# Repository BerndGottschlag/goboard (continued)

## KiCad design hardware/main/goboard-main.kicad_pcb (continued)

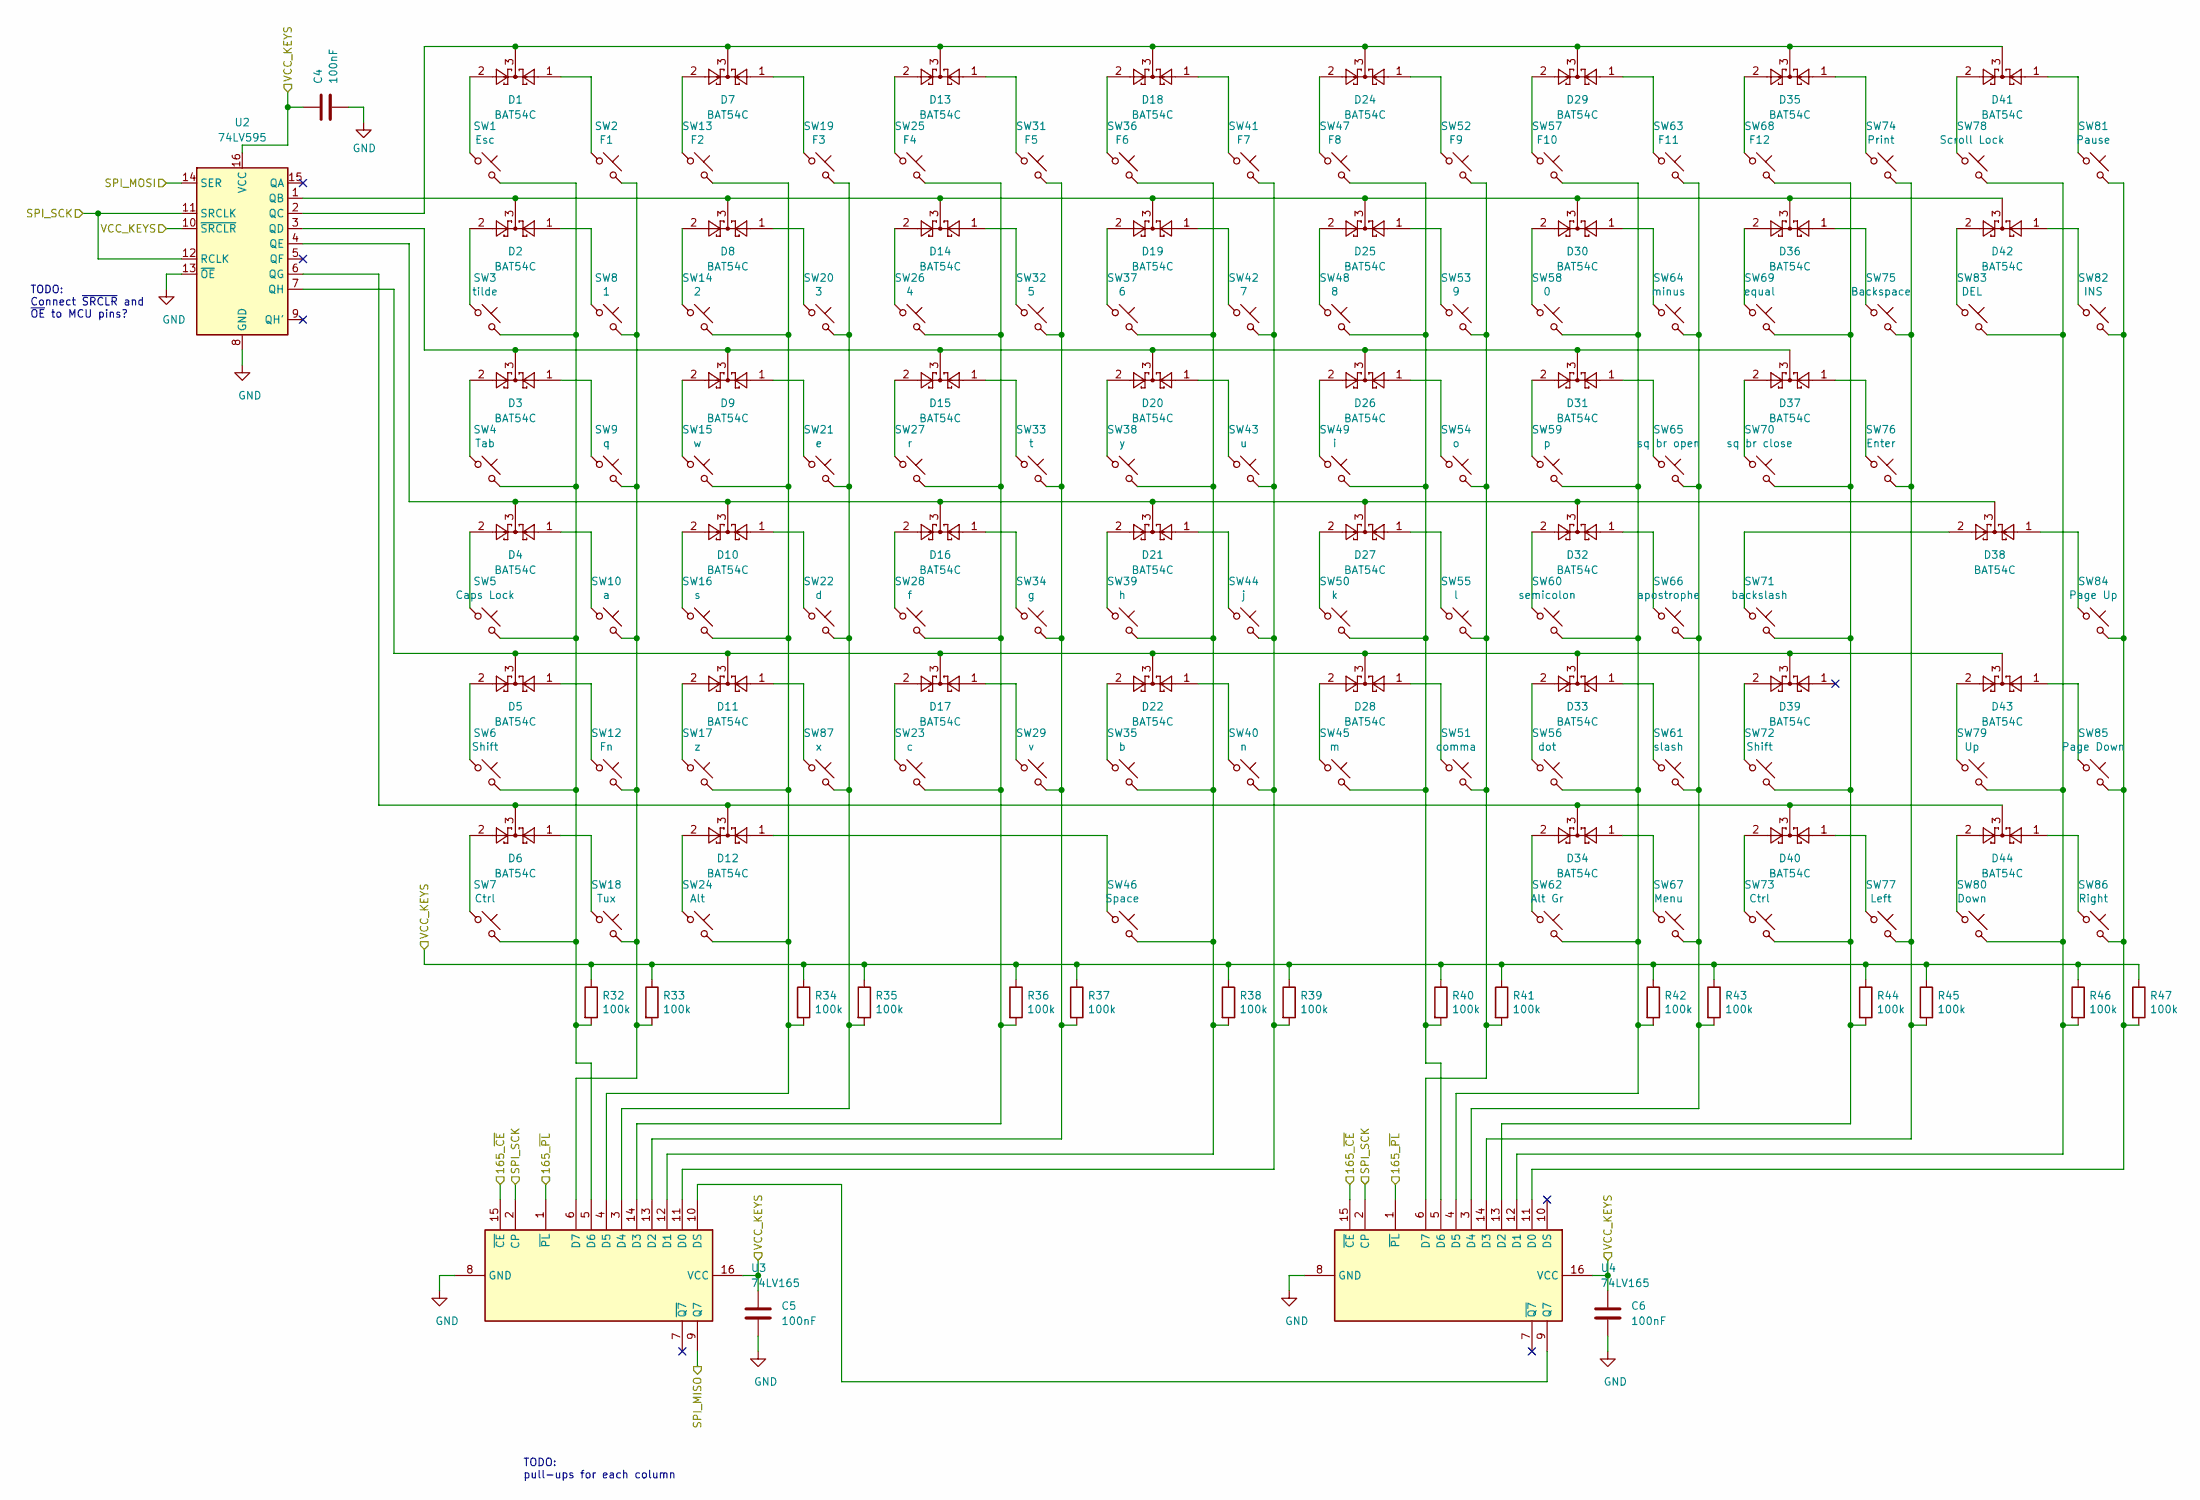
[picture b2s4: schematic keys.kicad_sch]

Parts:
C4, C5, C6: 100nF; C_0603_1608Metric_Pad1.08x0.95mm_HandSolder; Part Name 06033C104KAT4A; Mouser 581-06033C104KAT4A
D1, D2, D3, D4, D5, D6, D7, D8, D9, D10, D11, D12, D13, D14, D15, D16, D17, D18, D19, D20, D21, D22, D24, D25, D26, D27, D28, D29, D30, D31, D32, D33, D34, D35, D36, D37, D38, D39, D40, D41, D42, D43, D44: BAT54C; SOT-23; Part Name BAT54A; Mouser 241-BAT54A_R1_00001
R32, R33, R34, R35, R36, R37, R38, R39, R40, R41, R42, R43, R44, R45, R46, R47: 100k; R_0603_1608Metric_Pad0.98x0.95mm_HandSolder
SW1: Esc; SW_Cherry_MX_1.00u_PCB; Part Name MX1A-E1NW; Mouser 540-MX1A-E1NW
SW2: F1; SW_Cherry_MX_1.00u_PCB; Part Name MX1A-E1NW; Mouser 540-MX1A-E1NW
SW3: tilde; SW_Cherry_MX_1.00u_PCB; Part Name MX1A-E1NW; Mouser 540-MX1A-E1NW
SW4: Tab; SW_Cherry_MX_1.50u_PCB; Part Name MX1A-E1NW; Mouser 540-MX1A-E1NW
SW5: Caps Lock; SW_Cherry_MX_1.75u_PCB; Part Name MX1A-E1NW; Mouser 540-MX1A-E1NW
SW6: Shift; SW_Cherry_MX_1.25u_PCB; Part Name MX1A-E1NW; Mouser 540-MX1A-E1NW
SW7: Ctrl; SW_Cherry_MX_1.25u_PCB; Part Name MX1A-E1NW; Mouser 540-MX1A-E1NW
SW8: 1; SW_Cherry_MX_1.00u_PCB; Part Name MX1A-E1NW; Mouser 540-MX1A-E1NW
SW9: q; SW_Cherry_MX_1.00u_PCB; Part Name MX1A-E1NW; Mouser 540-MX1A-E1NW
SW10: a; SW_Cherry_MX_1.00u_PCB; Part Name MX1A-E1NW; Mouser 540-MX1A-E1NW
SW12: Fn; SW_Cherry_MX_1.00u_PCB; Part Name MX1A-E1NW; Mouser 540-MX1A-E1NW
SW13: F2; SW_Cherry_MX_1.00u_PCB; Part Name MX1A-E1NW; Mouser 540-MX1A-E1NW
SW14: 2; SW_Cherry_MX_1.00u_PCB; Part Name MX1A-E1NW; Mouser 540-MX1A-E1NW
SW15: w; SW_Cherry_MX_1.00u_PCB; Part Name MX1A-E1NW; Mouser 540-MX1A-E1NW
SW16: s; SW_Cherry_MX_1.00u_PCB; Part Name MX1A-E1NW; Mouser 540-MX1A-E1NW
SW17: z; SW_Cherry_MX_1.00u_PCB; Part Name MX1A-E1NW; Mouser 540-MX1A-E1NW
SW18: Tux; SW_Cherry_MX_1.25u_PCB; Part Name MX1A-E1NW; Mouser 540-MX1A-E1NW
SW19: F3; SW_Cherry_MX_1.00u_PCB; Part Name MX1A-E1NW; Mouser 540-MX1A-E1NW
SW20: 3; SW_Cherry_MX_1.00u_PCB; Part Name MX1A-E1NW; Mouser 540-MX1A-E1NW
SW21: e; SW_Cherry_MX_1.00u_PCB; Part Name MX1A-E1NW; Mouser 540-MX1A-E1NW
SW22: d; SW_Cherry_MX_1.00u_PCB; Part Name MX1A-E1NW; Mouser 540-MX1A-E1NW
SW23: c; SW_Cherry_MX_1.00u_PCB; Part Name MX1A-E1NW; Mouser 540-MX1A-E1NW
SW24: Alt; SW_Cherry_MX_1.25u_PCB; Part Name MX1A-E1NW; Mouser 540-MX1A-E1NW
SW25: F4; SW_Cherry_MX_1.00u_PCB; Part Name MX1A-E1NW; Mouser 540-MX1A-E1NW
SW26: 4; SW_Cherry_MX_1.00u_PCB; Part Name MX1A-E1NW; Mouser 540-MX1A-E1NW
SW27: r; SW_Cherry_MX_1.00u_PCB; Part Name MX1A-E1NW; Mouser 540-MX1A-E1NW
SW28: f; SW_Cherry_MX_1.00u_PCB; Part Name MX1A-E1NW; Mouser 540-MX1A-E1NW
SW29: v; SW_Cherry_MX_1.00u_PCB; Part Name MX1A-E1NW; Mouser 540-MX1A-E1NW
SW31: F5; SW_Cherry_MX_1.00u_PCB; Part Name MX1A-E1NW; Mouser 540-MX1A-E1NW
SW32: 5; SW_Cherry_MX_1.00u_PCB; Part Name MX1A-E1NW; Mouser 540-MX1A-E1NW
SW33: t; SW_Cherry_MX_1.00u_PCB; Part Name MX1A-E1NW; Mouser 540-MX1A-E1NW
SW34: g; SW_Cherry_MX_1.00u_PCB; Part Name MX1A-E1NW; Mouser 540-MX1A-E1NW
SW35: b; SW_Cherry_MX_1.00u_PCB; Part Name MX1A-E1NW; Mouser 540-MX1A-E1NW
SW36: F6; SW_Cherry_MX_1.00u_PCB; Part Name MX1A-E1NW; Mouser 540-MX1A-E1NW
SW37: 6; SW_Cherry_MX_1.00u_PCB; Part Name MX1A-E1NW; Mouser 540-MX1A-E1NW
SW38: y; SW_Cherry_MX_1.00u_PCB; Part Name MX1A-E1NW; Mouser 540-MX1A-E1NW
SW39: h; SW_Cherry_MX_1.00u_PCB; Part Name MX1A-E1NW; Mouser 540-MX1A-E1NW
SW40: n; SW_Cherry_MX_1.00u_PCB; Part Name MX1A-E1NW; Mouser 540-MX1A-E1NW
SW41: F7; SW_Cherry_MX_1.00u_PCB; Part Name MX1A-E1NW; Mouser 540-MX1A-E1NW
SW42: 7; SW_Cherry_MX_1.00u_PCB; Part Name MX1A-E1NW; Mouser 540-MX1A-E1NW
SW43: u; SW_Cherry_MX_1.00u_PCB; Part Name MX1A-E1NW; Mouser 540-MX1A-E1NW
SW44: j; SW_Cherry_MX_1.00u_PCB; Part Name MX1A-E1NW; Mouser 540-MX1A-E1NW
SW45: m; SW_Cherry_MX_1.00u_PCB; Part Name MX1A-E1NW; Mouser 540-MX1A-E1NW
SW46: Space; SW_Cherry_MX_6.25u_PCB; Part Name MX1A-E1NW; Mouser 540-MX1A-E1NW
SW47: F8; SW_Cherry_MX_1.00u_PCB; Part Name MX1A-E1NW; Mouser 540-MX1A-E1NW
SW48: 8; SW_Cherry_MX_1.00u_PCB; Part Name MX1A-E1NW; Mouser 540-MX1A-E1NW
SW49: i; SW_Cherry_MX_1.00u_PCB; Part Name MX1A-E1NW; Mouser 540-MX1A-E1NW
SW50: k; SW_Cherry_MX_1.00u_PCB; Part Name MX1A-E1NW; Mouser 540-MX1A-E1NW
SW51: comma; SW_Cherry_MX_1.00u_PCB; Part Name MX1A-E1NW; Mouser 540-MX1A-E1NW
SW52: F9; SW_Cherry_MX_1.00u_PCB; Part Name MX1A-E1NW; Mouser 540-MX1A-E1NW
SW53: 9; SW_Cherry_MX_1.00u_PCB; Part Name MX1A-E1NW; Mouser 540-MX1A-E1NW
SW54: o; SW_Cherry_MX_1.00u_PCB; Part Name MX1A-E1NW; Mouser 540-MX1A-E1NW
SW55: l; SW_Cherry_MX_1.00u_PCB; Part Name MX1A-E1NW; Mouser 540-MX1A-E1NW
SW56: dot; SW_Cherry_MX_1.00u_PCB; Part Name MX1A-E1NW; Mouser 540-MX1A-E1NW
SW57: F10; SW_Cherry_MX_1.00u_PCB; Part Name MX1A-E1NW; Mouser 540-MX1A-E1NW
SW58: 0; SW_Cherry_MX_1.00u_PCB; Part Name MX1A-E1NW; Mouser 540-MX1A-E1NW
SW59: p; SW_Cherry_MX_1.00u_PCB; Part Name MX1A-E1NW; Mouser 540-MX1A-E1NW
SW60: semicolon; SW_Cherry_MX_1.00u_PCB; Part Name MX1A-E1NW; Mouser 540-MX1A-E1NW
SW61: slash; SW_Cherry_MX_1.00u_PCB; Part Name MX1A-E1NW; Mouser 540-MX1A-E1NW
SW62: Alt Gr; SW_Cherry_MX_1.00u_PCB; Part Name MX1A-E1NW; Mouser 540-MX1A-E1NW
SW63: F11; SW_Cherry_MX_1.00u_PCB; Part Name MX1A-E1NW; Mouser 540-MX1A-E1NW
SW64: minus; SW_Cherry_MX_1.00u_PCB; Part Name MX1A-E1NW; Mouser 540-MX1A-E1NW
SW65: sq br open; SW_Cherry_MX_1.00u_PCB; Part Name MX1A-E1NW; Mouser 540-MX1A-E1NW
SW66: apostrophe; SW_Cherry_MX_1.00u_PCB; Part Name MX1A-E1NW; Mouser 540-MX1A-E1NW
SW67: Menu; SW_Cherry_MX_1.00u_PCB; Part Name MX1A-E1NW; Mouser 540-MX1A-E1NW
SW68: F12; SW_Cherry_MX_1.00u_PCB; Part Name MX1A-E1NW; Mouser 540-MX1A-E1NW
SW69: equal; SW_Cherry_MX_1.00u_PCB; Part Name MX1A-E1NW; Mouser 540-MX1A-E1NW
SW70: sq br close; SW_Cherry_MX_1.00u_PCB; Part Name MX1A-E1NW; Mouser 540-MX1A-E1NW
SW71: backslash; SW_Cherry_MX_1.00u_PCB; Part Name MX1A-E1NW; Mouser 540-MX1A-E1NW
SW72: Shift; SW_Cherry_MX_1.75u_PCB; Part Name MX1A-E1NW; Mouser 540-MX1A-E1NW
SW73: Ctrl; SW_Cherry_MX_1.00u_PCB; Part Name MX1A-E1NW; Mouser 540-MX1A-E1NW
SW74: Print; SW_Cherry_MX_1.00u_PCB; Part Name MX1A-E1NW; Mouser 540-MX1A-E1NW
SW75: Backspace; SW_Cherry_MX_2.00u_PCB; Part Name MX1A-E1NW; Mouser 540-MX1A-E1NW
SW76: Enter; SW_Cherry_MX_ISOEnter_PCB; Part Name MX1A-E1NW; Mouser 540-MX1A-E1NW
SW77: Left; SW_Cherry_MX_1.00u_PCB; Part Name MX1A-E1NW; Mouser 540-MX1A-E1NW
SW78: Scroll Lock; SW_Cherry_MX_1.00u_PCB; Part Name MX1A-E1NW; Mouser 540-MX1A-E1NW
SW79: Up; SW_Cherry_MX_1.00u_PCB; Part Name MX1A-E1NW; Mouser 540-MX1A-E1NW
SW80: Down; SW_Cherry_MX_1.00u_PCB; Part Name MX1A-E1NW; Mouser 540-MX1A-E1NW
SW81: Pause; SW_Cherry_MX_1.00u_PCB; Part Name MX1A-E1NW; Mouser 540-MX1A-E1NW
SW82: INS; SW_Cherry_MX_1.00u_PCB; Part Name MX1A-E1NW; Mouser 540-MX1A-E1NW
SW83: DEL; SW_Cherry_MX_1.00u_PCB; Part Name MX1A-E1NW; Mouser 540-MX1A-E1NW
SW84: Page Up; SW_Cherry_MX_1.00u_PCB; Part Name MX1A-E1NW; Mouser 540-MX1A-E1NW
SW85: Page Down; SW_Cherry_MX_1.00u_PCB; Part Name MX1A-E1NW; Mouser 540-MX1A-E1NW
SW86: Right; SW_Cherry_MX_1.00u_PCB; Part Name MX1A-E1NW; Mouser 540-MX1A-E1NW
SW87: x; SW_Cherry_MX_1.00u_PCB; Part Name MX1A-E1NW; Mouser 540-MX1A-E1NW
U2: 74LV595; TSSOP-16_4.4x5mm_P0.65mm; Mouser 771-74LV595PW-T
U3, U4: 74LV165; TSSOP-16_4.4x5mm_P0.65mm; Mouser 771-LV165PW112

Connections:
/MCU/165_~CE: U3.15 (~CE), U4.15 (~CE); also elsewhere on the board
/MCU/165_~PL: U3.1 (~PL), U4.1 (~PL); also elsewhere on the board
/MCU/SPI_MISO: U3.9 (Q7); also elsewhere on the board
/MCU/SPI_MOSI: U2.14 (SER); also elsewhere on the board
/MCU/SPI_SCK: U2.11 (SRCLK), U2.12 (RCLK), U3.2 (CP), U4.2 (CP); also elsewhere on the board
/VCC_KEYS: C4.1, C5.1, C6.1, R32.1, R33.1, R34.1, R35.1, R36.1, R37.1, R38.1, R39.1, R40.1, R41.1, R42.1, R43.1, R44.1, R45.1, R46.1, R47.1, U2.10 (~SRCLR), U2.16 (VCC), U3.16 (VCC), U4.16 (VCC); also elsewhere on the board
GND: C4.2, C5.2, C6.2, U2.8 (GND), U2.13 (~OE), U3.8 (GND), U4.8 (GND); also elsewhere on the board
unnamed: D1.1, SW2.1
unnamed: D1.2, SW1.1
unnamed: D1.3, D7.3, D13.3, D18.3, D24.3, D29.3, D35.3, D41.3, U2.2 (QC)
unnamed: D2.1, SW8.1
unnamed: D2.2, SW3.1
unnamed: D3.1, SW9.1
unnamed: D3.2, SW4.1
unnamed: D4.1, SW10.1
unnamed: D4.2, SW5.1
unnamed: D5.1, SW12.1
unnamed: D5.2, SW6.1
unnamed: D6.1, SW18.1
unnamed: D6.2, SW7.1
unnamed: D7.1, SW19.1
unnamed: D7.2, SW13.1
unnamed: D8.1, SW20.1
unnamed: D8.2, SW14.1
unnamed: D9.1, SW21.1
unnamed: D9.2, SW15.1
unnamed: D10.1, SW22.1
unnamed: D10.2, SW16.1
unnamed: D4.3, D10.3, D16.3, D21.3, D27.3, D32.3, D38.3, U2.4 (QE)
unnamed: D11.1, SW87.1
unnamed: D11.2, SW17.1
unnamed: D5.3, D11.3, D17.3, D22.3, D28.3, D33.3, D39.3, D43.3, U2.7 (QH)
unnamed: D12.1, SW46.1
unnamed: D12.2, SW24.1
unnamed: D6.3, D12.3, D34.3, D40.3, D44.3, U2.6 (QG)
unnamed: D13.1, SW31.1
unnamed: D13.2, SW25.1
unnamed: D14.1, SW32.1
unnamed: D14.2, SW26.1
unnamed: D2.3, D8.3, D14.3, D19.3, D25.3, D30.3, D36.3, D42.3, U2.1 (QB)
unnamed: D15.1, SW33.1
unnamed: D15.2, SW27.1
unnamed: D3.3, D9.3, D15.3, D20.3, D26.3, D31.3, D37.3, U2.3 (QD)
unnamed: D16.1, SW34.1
unnamed: D16.2, SW28.1
unnamed: D17.1, SW29.1
unnamed: D17.2, SW23.1
unnamed: D18.1, SW41.1
unnamed: D18.2, SW36.1
unnamed: D19.1, SW42.1
unnamed: D19.2, SW37.1
unnamed: D20.1, SW43.1
unnamed: D20.2, SW38.1
unnamed: D21.1, SW44.1
unnamed: D21.2, SW39.1
unnamed: D22.1, SW40.1
unnamed: D22.2, SW35.1
unnamed: D24.1, SW52.1
unnamed: D24.2, SW47.1
unnamed: D25.1, SW53.1
unnamed: D25.2, SW48.1
unnamed: D26.1, SW54.1
unnamed: D26.2, SW49.1
unnamed: D27.1, SW55.1
unnamed: D27.2, SW50.1
unnamed: D28.1, SW51.1
unnamed: D28.2, SW45.1
unnamed: D29.1, SW63.1
unnamed: D29.2, SW57.1
unnamed: D30.1, SW64.1
unnamed: D30.2, SW58.1
unnamed: D31.1, SW65.1
unnamed: D31.2, SW59.1
unnamed: D32.1, SW66.1
unnamed: D32.2, SW60.1
unnamed: D33.1, SW61.1
unnamed: D33.2, SW56.1
unnamed: D34.1, SW67.1
unnamed: D34.2, SW62.1
unnamed: D35.1, SW74.1
unnamed: D35.2, SW68.1
unnamed: D36.1, SW75.1
unnamed: D36.2, SW69.1
unnamed: D37.1, SW76.1
unnamed: D37.2, SW70.1
unnamed: D38.1, SW84.1
unnamed: D38.2, SW71.1
unnamed: D39.2, SW72.1
unnamed: D40.1, SW77.1
unnamed: D40.2, SW73.1
unnamed: D41.1, SW81.1
unnamed: D41.2, SW78.1
unnamed: D42.1, SW82.1
unnamed: D42.2, SW83.1
unnamed: D43.1, SW85.1
unnamed: D43.2, SW79.1
unnamed: D44.1, SW86.1
unnamed: D44.2, SW80.1
unnamed: R32.2, SW1.2, SW3.2, SW4.2, SW5.2, SW6.2, SW7.2, U3.5 (D6)
unnamed: R33.2, SW2.2, SW8.2, SW9.2, SW10.2, SW12.2, SW18.2, U3.6 (D7)
unnamed: R34.2, SW13.2, SW14.2, SW15.2, SW16.2, SW17.2, SW24.2, U3.4 (D5)
unnamed: R35.2, SW19.2, SW20.2, SW21.2, SW22.2, SW87.2, U3.3 (D4)
unnamed: R36.2, SW23.2, SW25.2, SW26.2, SW27.2, SW28.2, U3.14 (D3)
unnamed: R37.2, SW29.2, SW31.2, SW32.2, SW33.2, SW34.2, U3.13 (D2)
unnamed: R38.2, SW35.2, SW36.2, SW37.2, SW38.2, SW39.2, SW46.2, U3.12 (D1)
unnamed: R39.2, SW40.2, SW41.2, SW42.2, SW43.2, SW44.2, U3.11 (D0)
unnamed: R40.2, SW45.2, SW47.2, SW48.2, SW49.2, SW50.2, U4.5 (D6)
unnamed: R41.2, SW51.2, SW52.2, SW53.2, SW54.2, SW55.2, U4.6 (D7)
unnamed: R42.2, SW56.2, SW57.2, SW58.2, SW59.2, SW60.2, SW62.2, U4.4 (D5)
unnamed: R43.2, SW61.2, SW63.2, SW64.2, SW65.2, SW66.2, SW67.2, U4.3 (D4)
unnamed: R44.2, SW68.2, SW69.2, SW70.2, SW71.2, SW72.2, SW73.2, U4.13 (D2)
unnamed: R45.2, SW74.2, SW75.2, SW76.2, SW77.2, U4.14 (D3)
unnamed: R46.2, SW78.2, SW79.2, SW80.2, SW83.2, U4.12 (D1)
unnamed: R47.2, SW81.2, SW82.2, SW84.2, SW85.2, SW86.2, U4.11 (D0)
unnamed: U3.10 (DS), U4.9 (Q7)

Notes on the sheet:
TODO: Connect ~SRCLR and ~OE to MCU pins?
TODO: pull-ups for each column

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
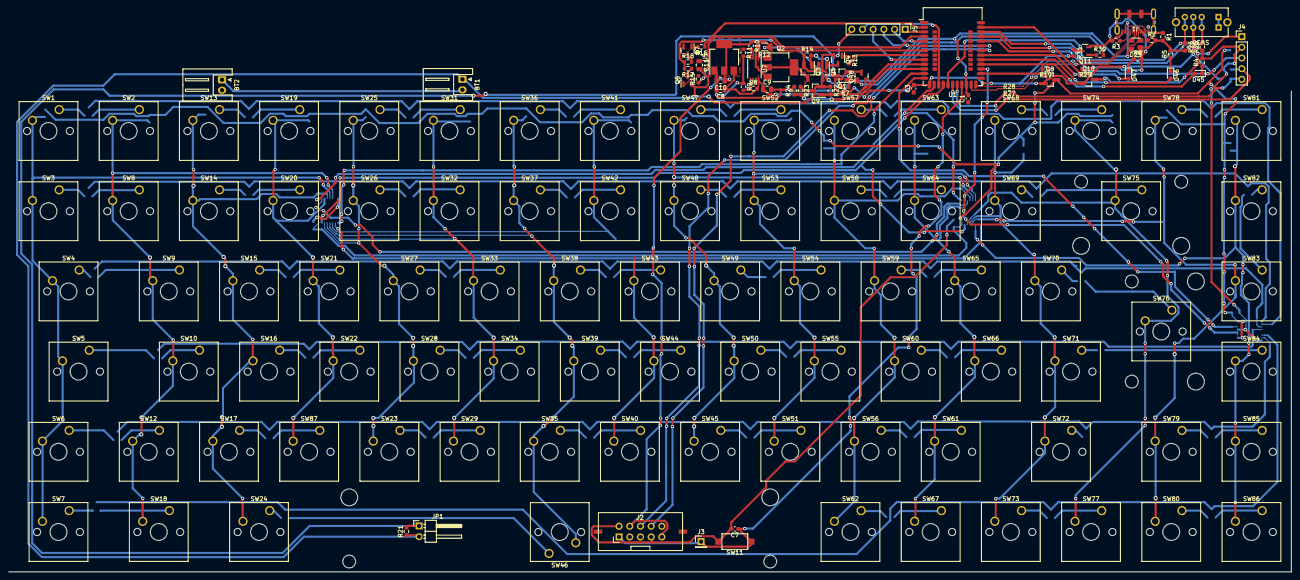
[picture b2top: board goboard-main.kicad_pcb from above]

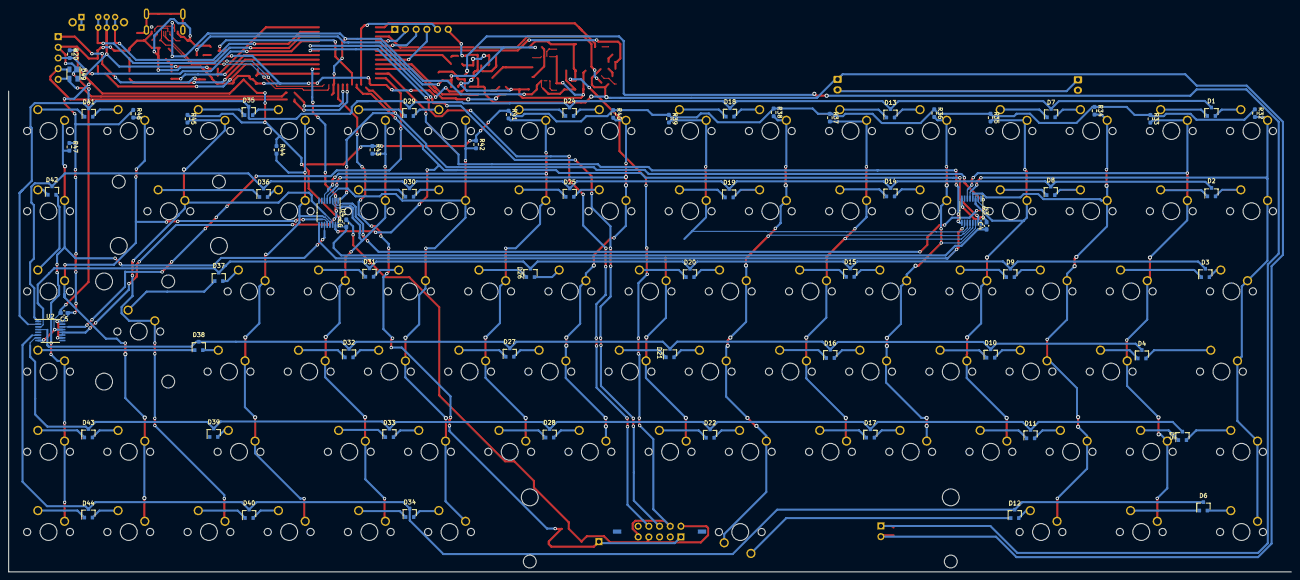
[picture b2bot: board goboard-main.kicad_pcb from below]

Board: 2 copper layers, 218 parts (67 on the bottom side), 171 nets.

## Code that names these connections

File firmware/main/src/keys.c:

#include "keys.h"

#include "app_timer.h"
#include "nrf_gpio.h"
#include "nrf_drv_spi.h"

#include <string.h>

#ifdef TEST_SETUP

#define TEST_KEY NRF_GPIO_PIN_MAP(1, 2)

#else

#define SPI_SCK_PIN NRF_GPIO_PIN_MAP(1, 0)
#define SPI_MISO_PIN NRF_GPIO_PIN_MAP(0, 4)
#define SPI_MOSI_PIN NRF_GPIO_PIN_MAP(0, 5)
#define LOAD_PIN NRF_GPIO_PIN_MAP(0, 7)
#define STORE_PIN NRF_GPIO_PIN_MAP(0, 12)

#define NUMPAD_RX_PIN NRF_GPIO_PIN_MAP(0, 21)
#define NUMPAD_TX_PIN NRF_GPIO_PIN_MAP(0, 19)
#define NUMPAD_ID_PIN NRF_GPIO_PIN_MAP(1, 4)

#define ENABLE_KEY_POWER_PIN NRF_GPIO_PIN_MAP(0, 22)
#define ENABLE_NUMPAD_POWER_PIN NRF_GPIO_PIN_MAP(1, 4)

/**
 * SPI for the key matrix shift registers.
 */
static const nrf_drv_spi_t spi = NRF_DRV_SPI_INSTANCE(0);

#endif

/**
 * Timer for periodic sampling of the numpad ID line.
 */
APP_TIMER_DEF(numpad_id_timer);

static struct key_bitmap key_state = EMPTY_KEY_BITMAP;

void key_bitmap_set(struct key_bitmap *bitmap, int scancode) {
	uint32_t word = scancode >> 5;
	uint32_t bit = scancode & 0x1f;
	bitmap->keys[word] |= 1 << bit;
}

void key_bitmap_clear(struct key_bitmap *bitmap, int scancode) {
	uint32_t word = scancode >> 5;
	uint32_t bit = scancode & 0x1f;
	bitmap->keys[word] &= ~(1 << bit);
}

void legacy_key_list_from_bitmap(const struct key_bitmap *bitmap,
                                 struct legacy_key_list *list) {
	/* TODO */
}

static void numpad_id_timer_handler(void *context) {
	/* TODO */
}

void keys_init(void) {
	ret_code_t ret;

	ret = app_timer_create(&numpad_id_timer,
	                       APP_TIMER_MODE_REPEATED,
	                       numpad_id_timer_handler);
	APP_ERROR_CHECK(ret);

	/* TODO */
}

void keys_activate(void) {
	/* TODO */
}

void keys_deactivate(void) {
	/* TODO */
}

void keys_activate_numpad(void) {
	/* TODO */
}

void keys_deactivate_numpad(void) {
	/* TODO */
}

void keys_set_num_lock_led(bool state) {
	/* TODO */
}

void keys_get_state(struct key_bitmap *bitmap) {
	memcpy(bitmap, &key_state, sizeof(key_state));
}

bool keys_poll(bool pause) {
	struct key_bitmap previous_key_state = key_state;

#ifdef TEST_SETUP
	bool test_key_state = nrf_gpio_pin_read(TEST_KEY);
	if (test_key_state) {
		key_bitmap_set(&key_state, KEY_K);
	} else {
		key_bitmap_clear(&key_state, KEY_K);
	}
	/* TODO: debouncing, pause */
#else
	/* TODO */
#endif
	return memcmp(&key_state, &previous_key_state, sizeof(key_state)) != 0;
}

void keys_prepare_system_off(void) {
	/* TODO */
}

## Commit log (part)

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2020-12-23 hardware: Add empty Kicad projects.
2020-12-23 Add README/LICENSE.
2020-12-25 Add keyboard layout and necessary 3d packages
2020-12-28 Implement the key matrix on the PCB
2020-12-29 Add a symbol for the Holyiot-18010-NRF52840
2020-12-29 Add footprint for the Holyiot-18010-NRF5284
2020-12-30 Add first schematic for the numpad
2020-12-31 Fix pin of the symbol of the Holyiot breakout board
2020-12-31 Add footprint for the USB-C jack JAE DX07S016JA1R1500
2021-01-01 Add 3d package for the usb jack
2021-01-01 Update the PCB
2021-01-01 Add connector to the numpad to the schematic
2021-01-01 WIP: numpad with an ATtiny
    As the newer versions of the ATtiny cannot be programmed using an
    In-Circuit-Programmer based on SPI this variant is not pursued further.
2021-01-02 Exchange the ATtiny with a STM32L011F4P6 for the numpad
2021-01-02 Modify the connection to the numpad
    As the numpad now uses a stm-microcontroller instead of the
    shift-registers the connection is changed to UART.
2021-01-02 Add programming/debug connection
2021-01-02 Fix MISO label for the shift registers
2021-01-02 Remove UART line from the NRF to the numpad
2021-01-02 Add footprints to many symbols
2021-01-02 Update PCB
2021-01-03 Add annotations
2021-01-03 Add specialized connector for the programming port
2021-01-09 Adapt the layout for another keycap set
    The layout is now compatible with this keycap set:
    https://hk-gaming.com/collections/keycaps/products/hk-gaming-dye-
    sublimation-cherry-profile-thick-pbt-keysets-for-mechanical-keyboard-139
    -keys-chalk
2021-01-09 Add outline of a shrouded pin header to the programming connector
2021-01-16 Add power supply from the debugging connector
    The batteries have to be disconnected when the debugger is plugged in,
    as the voltages differ (ca. 2V for the batteries, 3.3V for the
    debugger).
2021-01-16 Add kicad autosave files to gitignore
2021-01-16 Add new board outline
    Reason: This makes the first design iteration of the case possible.
2021-01-16 Add first rough version of the numpad PCB
2021-01-16 Redo board edge outline
2021-01-16 Fix path to the 3d model of the USB-C jack
2021-01-20 Write out the symbol names for the keys
2021-01-20 Add MCU-controlled battery balancing.
2021-01-20 Revert to a key layout with a menu key between alt gr and ctrl
2021-01-20 Fix power supply footprints and set references.
2021-01-23 Add signal to tell the MCU that USB is connected.
2021-01-24 Add footprint and 3D-model for the sliding switch
2021-01-24 Assign footprints
2021-01-24 Fix errors found by ERC
2021-01-25 Add an empty firmware project.
2021-01-25 Add circuit to disconnect the shift registers
    This is done to save energy when the keyboard is switched off.
2021-01-25 Add battery voltage measurement circuit
2021-01-25 Rework the off/bluetooth1/bluetooth2 switch connection
    To save energy an external pull-down resistor is added and the off
    position is not connected to the MCU.
2021-01-25 Remove the USB sense curcuit
    As V_BUS is connected to the MCU it can detect when the USB is
    connected.
2021-01-25 Rework the connection to the numpad
    Changes:
    - The UART lines now have a protection circuit
    - The power supply line of the numpad can be switched on and off by the MCU.
    - An Id-line is added so that the MCU can detect when the numpad is
    connected.
2021-01-25 Update the connection of the numpad
    The ID line is added to the numpad side and the connector pin assignment
    is updated.
2021-01-25 Fix symbol for the Holyiot board
    V_BUS pin was missing from the symbol.
2021-01-28 firmware: Add clock initialization and a separate library for the SDK.
2021-01-28 firmware: Compile with softdevice.
2021-01-28 firmware: Implement a USB HID device.
2021-01-30 Re-add USB voltage sense circuit
    Due to firmware limitations the USB voltage cannot be used directly for
    waking up the microcontroller.
2021-01-30 firmware: Fix HardFault breakpoint.
2021-01-30 firmware: Compile everything required for bluetooth.
2021-01-30 firmware: Add bluetooth and UART logging to the configuration.
2021-01-30 firmware: Use the NRF SDK scheduler and power management.
    This change breaks the timers currently used in key_matrix.c, but that code
    is rewritten anyways.
2021-01-30 Add the USB sense circuit to the PCB
2021-01-31 firmware: Start to rework power management code.
2021-01-31 firmware: Add a simple mode LED.
2021-01-31 Add pull-up resistors to the key matrix
2021-02-02 Changes due to updated kicad version
2021-02-04 Add ground planes
2021-02-05 Fix DRC errors
    Among others:
    - Arrange part identifiers on silkscreen
    - Fix clearance errors
2021-02-06 Change position of the battery connectors
    The previous position collided with the switches.
2021-02-06 Fix DRC errors
2021-02-06 Fix footprint for the debugging connector
2021-02-06 hardware: Change key matrix/numpad voltage to be off by default.
2021-02-06 hardware: Use contiguous pins for the rows.
    Contiguous pins simplify programming as we can just shift a bit in a loop.
2021-02-06 Numpad: WIP: design PCB
2021-02-06 Numpad: Fix labels of columns and rows of the key matrix
2021-02-06 Numpad: Fix DRC errors
    Mainly placement of silkscreen content, track clearance violations and
    overlapping courtyards.
2021-02-06 Add footprints to two components
2021-02-06 Numpad: Add last traces and ground plane
2021-02-06 Numpad: Create traces from the MCU to the keymatrix
2021-02-07 Main: Fix position of the Power-LED
2021-02-07 Main: Transfer the changes of Mathias Gottschlag to PCB
    Transfered changes of commits:
    17ca2a9548b7ad5bcafb4c4489e0f86f719de1c1
    726a2ce27092844aff245bdad9676d5f44ab9ae4
    f3c8f86b82ee067a7bff6dfa5026467c1d0aa33d
2021-02-09 Add separate LOAD and STORE connections to the shift registers.
2021-02-13 Numpad: Fix position of the power-led
2021-02-13 Improve routing of a track
2021-02-13 Main: Improve board outlines
    Add rounded corners and make the outline a bit smaller
2021-02-13 Main: Modify design rules for JLCPCB
2021-02-13 Main: Fix errors found by the modified design rules check
2021-02-13 Main: Fix datasheet link of the usb jack
2021-02-13 Main: Tidy up traces and ground plates
2021-02-13 Main: Add a fuse to BATT+
2021-02-13 Main: Review of schematics
2021-02-13 Review and fix footprints
2021-02-13 Main: Update pcb
    Add pull-up resistor for RESET.
2021-02-20 Numpad: Rework PCB layout
    The Power-LED was eliminated and the Numpad-LED moved off the board.
2021-02-20 Numpad: Add break-away board with the numpad LED
2021-02-20 Numpad: Adjust the board outline of the break-away tab
2021-02-20 Numpad: Exchange the debug-conn footprint for one without silkscreen
2021-02-20 Numpad: Configure designrules for JLCPCB + Fix Errors
2021-02-21 Numpad: Update PCB
    The footprint of two capacitors were changed.
2021-02-21 Update .gitignore to exclude bom files generated by kicad
2021-02-21 Numpad: Add pullup for reset and connect BOOT0 to ground
2021-02-21 Numpad: Add power flag to satisfy the ERC
2021-02-21 Main & Numpad: Fix the pin-out of the programmer connector
2021-02-21 Main: Update symbols
2021-02-22 Main: WIP: Add mounting holes
2021-02-22 Main & Numpad: Exchange unavailable capacitors
2021-02-22 Main: Fix footprint assignment of part
2021-02-27 Main: Add mounting holes
2021-02-27 hardware: Various small PCB and schematics fixes/improvements.
    - 3.3V and 3.3V_programmer used to be the same net.
    - Lots of ground plane fixes for a more contiguous ground plane.
    - Reordered some MCU pins for a better layout.
2021-02-28 Numpad: Re-route traces to improve ground plane
2021-02-28 main: Ground plane repairs, via stitching.
2021-02-28 Main & Numpad: Add release info to PCBs
2021-02-28 Numpad: Add gerber setup and update groundplane fill
2021-03-03 firmware: List of key codes.
2021-03-03 firmware: Add stubs for new key API.
2021-03-03 firmware: high frequency clock initialization.
2021-03-03 firmware: Make the mode switch profiles configurable.
2021-03-03 firmware: Fix compiling.
2021-03-03 firmware: Add more API documentation.
2021-03-03 firmware: Add Doxyfile for source code documentation.
2021-03-03 unifying: Send more than one key code.
2021-03-09 firmware: New zephyr project.
2021-03-13 firmware: C++ stubs for power supply and mode switch.
2021-03-13 firmware: Make gdb break on hard faults, use st-link instead of cmsis-dap.
2021-03-13 firmware: Add missing exception class.
2021-03-13 Add .gdb_history to .gdbignore.
2021-03-13 firmware: Add testing support and fix compile/program scripts.
2021-03-13 firmware: Stub classes for key matrix and debouncing.
2021-03-13 firmware: Let a LED blink for debugging.
2021-03-14 firmware: Move key codes to C++.
2021-03-15 firmware: Add key/scancode mapping and a corresponding test.
2021-03-15 Remove two unnecessary nrf5 SDK configuration files.
2021-03-15 firmware: Add test for debouncing.
2021-03-19 firmware: Add stubs for the power supply code.
2021-03-19 firmware: Add tests for the battery charging logic.
2021-03-20 firmware: Add mode switch API stubs.
2021-03-20 firmware: Remove lots of outdated C code.
2021-03-20 firmware: Add some dummy return values to make the main keyboard code work.
2021-03-20 firmware: Misc minor fixes.
2021-03-21 firmware: Add missing configuration for USB.
2021-03-21 firmware: Update to recent Zephyr.
2021-03-23 firmware: Add power supply pins to the device tree.
2021-03-28 Hardware main: correct datasheets of shift registers
2021-03-28 Main: Firmware: Add key mapping
2021-03-28 Main: Firmware: Fix key mapping (support duplicated key mappings).
    KEY_INVALID appeared multiple times in the key matrix mapping, so the
    second occurance overwrote the first. As the key bitmap is initially
    cleared anyways, the clear_bit() for non-pressed keys can be removed to
    prevent this behavior.
2021-03-28 Main: Firmware: Implement measuring the battery voltage.
    The state of charge is not calculated yet, and the USB connection is not
    yet detected.
2021-03-29 Main: Firmware: Implement power supply state callbacks.
2021-03-29 Main: Firmware: Fix a race condition on PowerSupply::has_usb_connection().
2021-03-30 Main: Firmware: Rename parameters in power_supply.hpp to match .cpp.
2021-03-30 Main: Firmware: Test KeyBitmap::bit_is_set() and fix tests.
2021-03-30 Main: Firmware: Add code to get 6 pressed keys for the HID boot protocol.
2021-03-30 Main: Firmware: Send pressed keys via USB HID.
2021-03-31 Main: Firmware: Fix USB SOF events and key change detection.
2021-03-31 Main: Firmware: Swap key rows to match the hardware.
2021-03-31 Main: Firmware: Remove more outdated C code.
2021-03-31 Main: Firmware: Remove some UART debug spam.
2021-03-31 Main: Firmware: Implement the mode switch.
2021-04-02 Main: Firmware: Stub functions for the LEDs.
2021-04-02 Main: Firmware: Add some stub functions for bluetooth support.
2021-04-02 Main: Firmware: Add some stub functions for unifying support.
2021-04-05 Main: Firmware: Fix compiling the tests, do not compile mode_switch.cpp.
2021-04-05 Main: Firmware: Add stub code to translate FN key combinations and tests.
2021-04-11 WIP: Unifying radio.
2021-05-09 Main: Firmware: Add debouncing
2021-06-07 firmware: Update the README.md, we do not use the old NRF SDK anymore.
2023-01-15 Translate first parts of the firmware to Rust.
    This commit includes a translation of the key matrix readout code to Rust.
    The hardware interface does not appear to work yet.
2023-02-04 firmware: Fix SPI settings in the Rust code.
2023-02-04 firmware: Fix the rust workspace file.
2023-02-04 Added a unit test for the battery charging code.
2023-02-04 Added the workspace Cargo.lock.
2023-11-20 defmt fixes for profiling
2024-02-04 Update embassy.
2024-02-04 Dispatcher stub code.
2024-02-04 Use probe-rs instead of probe-run.
2024-02-04 Implement battery charging hardware (ADC, pins).
2024-02-05 Add hardware-specific code for USB connection detection.
2024-02-16 Fix compiler errors due to embassy update.
2024-02-16 rustfmt, .gitignore
2024-02-16 Improve structure of the main task and construct a dispatcher.
2024-02-16 Fix some warnings.
2024-03-05 Dispatcher code for a simple USB keyboard.
2024-03-05 Wake up when USB is connected.
